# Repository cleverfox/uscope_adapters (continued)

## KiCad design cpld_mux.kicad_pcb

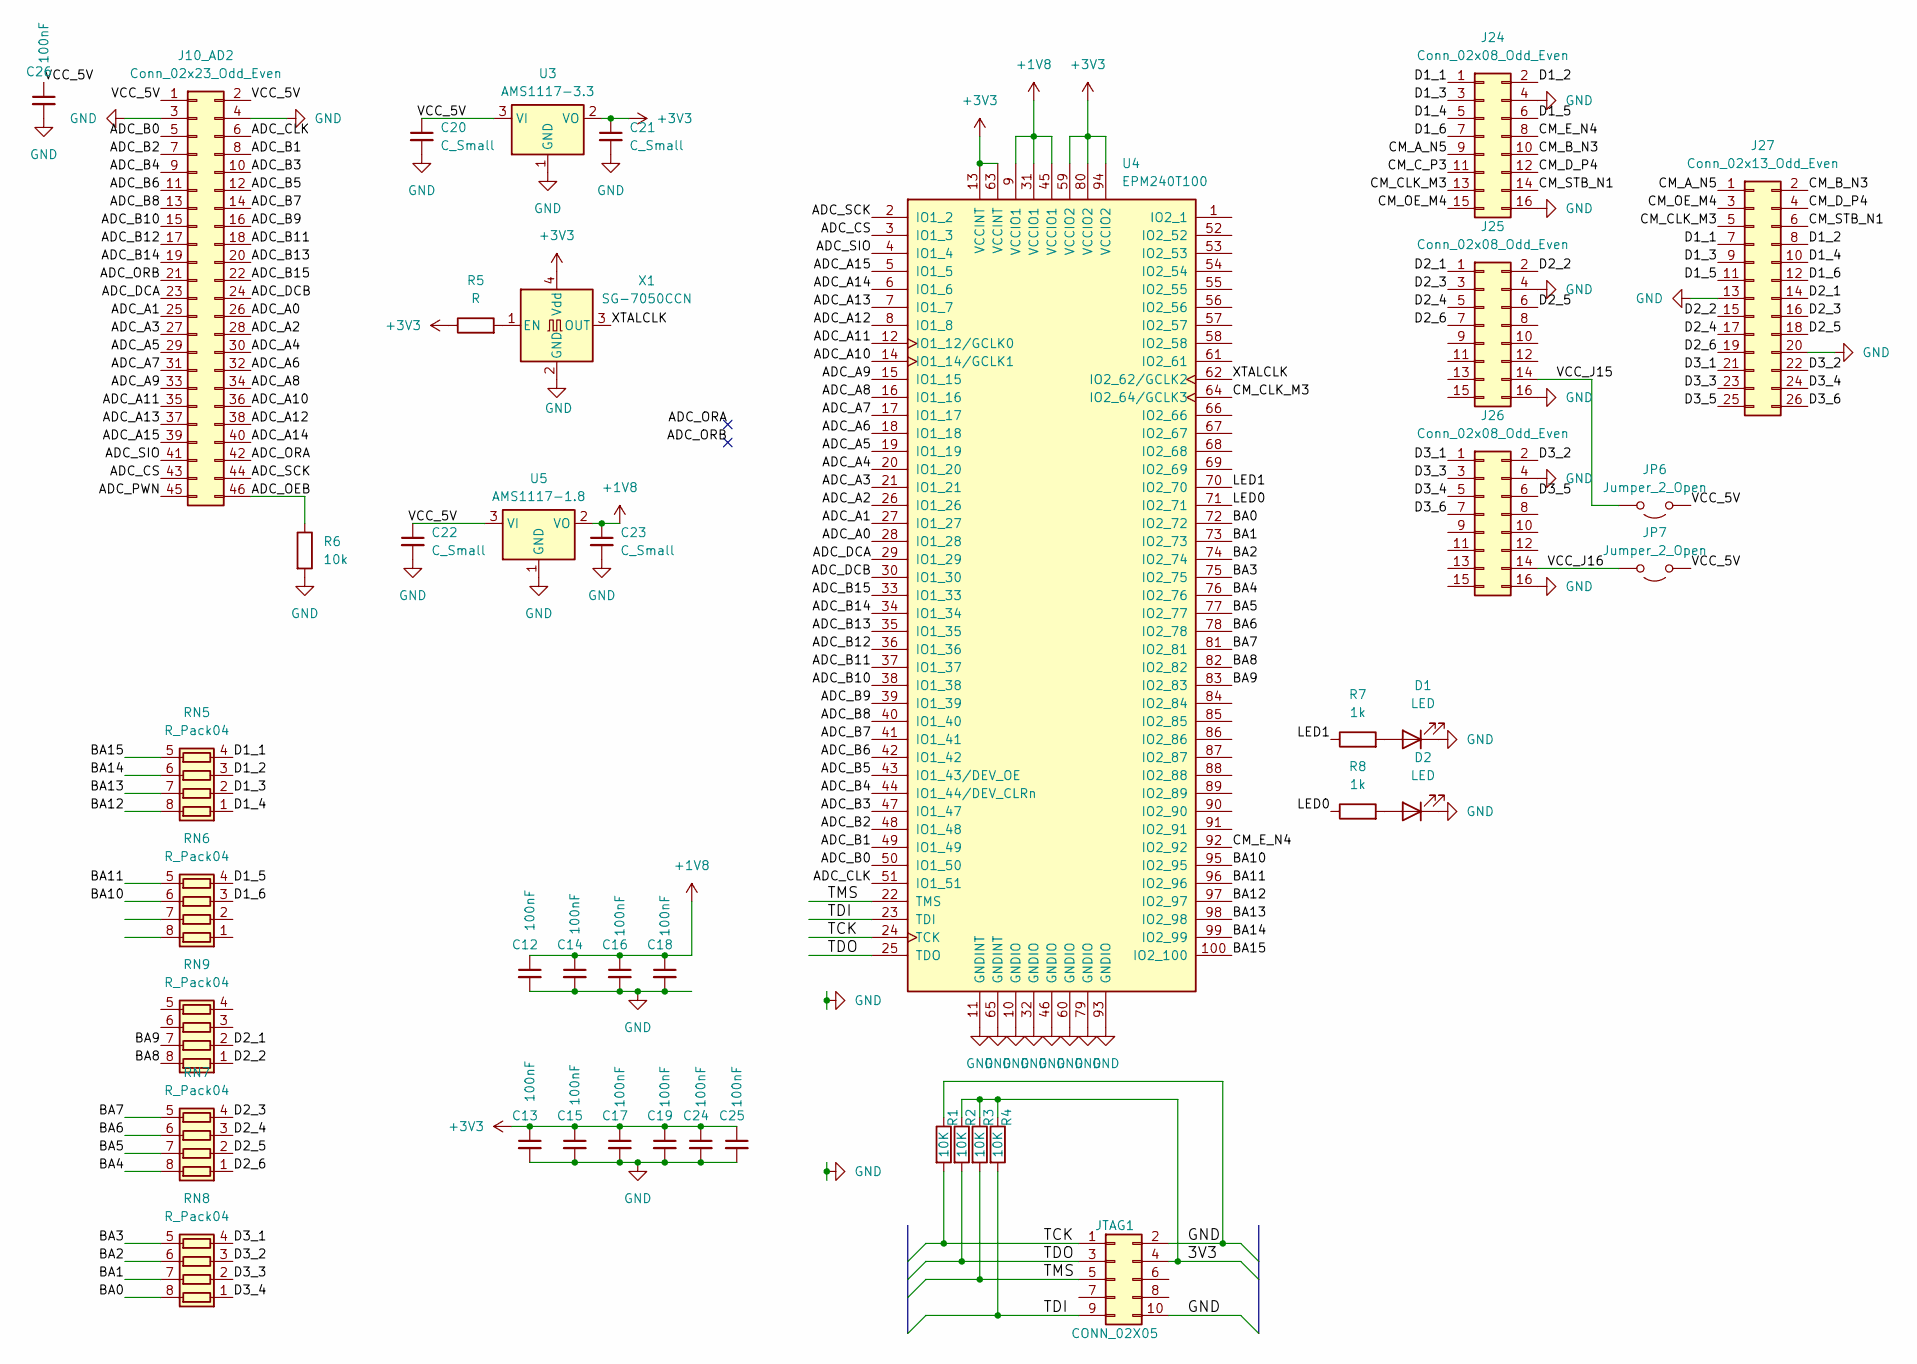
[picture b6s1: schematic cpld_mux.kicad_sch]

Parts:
C12, C13, C14, C15, C16, C17, C18, C19, C24, C25, C26: 100nF; C_0805_2012Metric
C20, C21, C22, C23: C_Small; C_0805_2012Metric
D1, D2: LED; LED_0805_2012Metric
J10_AD2: Conn_02x23_Odd_Even; PinSocket_2x23_P2.54mm_Vertical
J24, J25, J26: Conn_02x08_Odd_Even; PinSocket_2x08_P2.54mm_Vertical
J27: Conn_02x13_Odd_Even; PinHeader_2x13_P2.54mm_Vertical
JP6, JP7: Jumper_2_Open; SolderJumper-3_P1.3mm_Open_Pad1.0x1.5mm
JTAG1: CONN_02X05; PinHeader_2x05_P2.54mm_Vertical
R1, R2, R3, R4: 10K; R_0603_1608Metric_Pad0.98x0.95mm_HandSolder
R5: R; R_0603_1608Metric_Pad0.98x0.95mm_HandSolder
R6: 10k
R7, R8: 1k; R_0805_2012Metric
RN5, RN6, RN7, RN8, RN9: R_Pack04; R_Array_Convex_4x0603
U3: AMS1117-3.3; SOT-223-3_TabPin2
U4: EPM240T100; LQFP-100_14x14mm_P0.5mm
U5: AMS1117-1.8; SOT-223-3_TabPin2
X1: SG-7050CCN; Oscillator_SMD_Abracon_ASV-4Pin_7.0x5.1mm

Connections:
+1V8: C12.1, C14.1, C16.1, C18.1, C23.1, U4.9 (VCCIO1), U4.31 (VCCIO1), U4.45 (VCCIO1), U5.2 (VO)
+3V3: C13.1, C15.1, C17.1, C19.1, C21.1, C24.1, C25.1, R5.1, U3.2 (VO), U4.13 (VCCINT), U4.59 (VCCIO2), U4.63 (VCCINT), U4.80 (VCCIO2), U4.94 (VCCIO2), X1.4 (Vdd)
/cpld_mux/3V3: JTAG1.4, R2.1, R3.1, R4.1
/cpld_mux/ADC_A0: J10_AD2.26, U4.28 (IO1_28)
/cpld_mux/ADC_A1: J10_AD2.25, U4.27 (IO1_27)
/cpld_mux/ADC_A2: J10_AD2.28, U4.26 (IO1_26)
/cpld_mux/ADC_A3: J10_AD2.27, U4.21 (IO1_21)
/cpld_mux/ADC_A4: J10_AD2.30, U4.20 (IO1_20)
/cpld_mux/ADC_A5: J10_AD2.29, U4.19 (IO1_19)
/cpld_mux/ADC_A6: J10_AD2.32, U4.18 (IO1_18)
/cpld_mux/ADC_A7: J10_AD2.31, U4.17 (IO1_17)
/cpld_mux/ADC_A8: J10_AD2.34, U4.16 (IO1_16)
/cpld_mux/ADC_A9: J10_AD2.33, U4.15 (IO1_15)
/cpld_mux/ADC_A10: J10_AD2.36, U4.14 (IO1_14/GCLK1)
/cpld_mux/ADC_A11: J10_AD2.35, U4.12 (IO1_12/GCLK0)
/cpld_mux/ADC_A12: J10_AD2.38, U4.8 (IO1_8)
/cpld_mux/ADC_A13: J10_AD2.37, U4.7 (IO1_7)
/cpld_mux/ADC_A14: J10_AD2.40, U4.6 (IO1_6)
/cpld_mux/ADC_A15: J10_AD2.39, U4.5 (IO1_5)
/cpld_mux/ADC_B0: J10_AD2.5, U4.50 (IO1_50)
/cpld_mux/ADC_B1: J10_AD2.8, U4.49 (IO1_49)
/cpld_mux/ADC_B2: J10_AD2.7, U4.48 (IO1_48)
/cpld_mux/ADC_B3: J10_AD2.10, U4.47 (IO1_47)
/cpld_mux/ADC_B4: J10_AD2.9, U4.44 (IO1_44/DEV_CLRn)
/cpld_mux/ADC_B5: J10_AD2.12, U4.43 (IO1_43/DEV_OE)
/cpld_mux/ADC_B6: J10_AD2.11, U4.42 (IO1_42)
/cpld_mux/ADC_B7: J10_AD2.14, U4.41 (IO1_41)
/cpld_mux/ADC_B8: J10_AD2.13, U4.40 (IO1_40)
/cpld_mux/ADC_B9: J10_AD2.16, U4.39 (IO1_39)
/cpld_mux/ADC_B10: J10_AD2.15, U4.38 (IO1_38)
/cpld_mux/ADC_B11: J10_AD2.18, U4.37 (IO1_37)
/cpld_mux/ADC_B12: J10_AD2.17, U4.36 (IO1_36)
/cpld_mux/ADC_B13: J10_AD2.20, U4.35 (IO1_35)
/cpld_mux/ADC_B14: J10_AD2.19, U4.34 (IO1_34)
/cpld_mux/ADC_B15: J10_AD2.22, U4.33 (IO1_33)
/cpld_mux/ADC_CLK: J10_AD2.6, U4.51 (IO1_51)
/cpld_mux/ADC_CS: J10_AD2.43, U4.3 (IO1_3)
/cpld_mux/ADC_DCA: J10_AD2.23, U4.29 (IO1_29)
/cpld_mux/ADC_DCB: J10_AD2.24, U4.30 (IO1_30)
/cpld_mux/ADC_OEB: J10_AD2.46, R6.1
/cpld_mux/ADC_ORA: J10_AD2.42
/cpld_mux/ADC_ORB: J10_AD2.21
/cpld_mux/ADC_PWN: J10_AD2.45
/cpld_mux/ADC_SCK: J10_AD2.44, U4.2 (IO1_2)
/cpld_mux/ADC_SIO: J10_AD2.41, U4.4 (IO1_4)
/cpld_mux/BA0: RN8.8 (R1.2), U4.72 (IO2_72)
/cpld_mux/BA1: RN8.7 (R2.2), U4.73 (IO2_73)
/cpld_mux/BA2: RN8.6 (R3.2), U4.74 (IO2_74)
/cpld_mux/BA3: RN8.5 (R4.2), U4.75 (IO2_75)
/cpld_mux/BA4: RN7.8 (R1.2), U4.76 (IO2_76)
/cpld_mux/BA5: RN7.7 (R2.2), U4.77 (IO2_77)
/cpld_mux/BA6: RN7.6 (R3.2), U4.78 (IO2_78)
/cpld_mux/BA7: RN7.5 (R4.2), U4.81 (IO2_81)
/cpld_mux/BA8: RN9.8 (R1.2), U4.82 (IO2_82)
/cpld_mux/BA9: RN9.7 (R2.2), U4.83 (IO2_83)
/cpld_mux/BA10: RN6.6 (R3.2), U4.95 (IO2_95)
/cpld_mux/BA11: RN6.5 (R4.2), U4.96 (IO2_96)
/cpld_mux/BA12: RN5.8 (R1.2), U4.97 (IO2_97)
/cpld_mux/BA13: RN5.7 (R2.2), U4.98 (IO2_98)
/cpld_mux/BA14: RN5.6 (R3.2), U4.99 (IO2_99)
/cpld_mux/BA15: RN5.5 (R4.2), U4.100 (IO2_100)
/cpld_mux/CM_A_N5: J24.9, J27.1
/cpld_mux/CM_B_N3: J24.10, J27.2
/cpld_mux/CM_CLK_M3: J24.13, J27.5, U4.64 (IO2_64/GCLK3)
/cpld_mux/CM_C_P3: J24.11
/cpld_mux/CM_D_P4: J24.12, J27.4
/cpld_mux/CM_E_N4: J24.8, U4.92 (IO2_92)
/cpld_mux/CM_OE_M4: J24.15, J27.3
/cpld_mux/CM_STB_N1: J24.14, J27.6
/cpld_mux/D1_1: J24.1, J27.7, RN5.4 (R4.1)
/cpld_mux/D1_2: J24.2, J27.8, RN5.3 (R3.1)
/cpld_mux/D1_3: J24.3, J27.9, RN5.2 (R2.1)
/cpld_mux/D1_4: J24.5, J27.10, RN5.1 (R1.1)
/cpld_mux/D1_5: J24.6, J27.11, RN6.4 (R4.1)
/cpld_mux/D1_6: J24.7, J27.12, RN6.3 (R3.1)
/cpld_mux/D2_1: J25.1, J27.14, RN9.2 (R2.1)
/cpld_mux/D2_2: J25.2, J27.15, RN9.1 (R1.1)
/cpld_mux/D2_3: J25.3, J27.16, RN7.4 (R4.1)
/cpld_mux/D2_4: J25.5, J27.17, RN7.3 (R3.1)
/cpld_mux/D2_5: J25.6, J27.18, RN7.2 (R2.1)
/cpld_mux/D2_6: J25.7, J27.19, RN7.1 (R1.1)
/cpld_mux/D3_1: J26.1, J27.21, RN8.4 (R4.1)
/cpld_mux/D3_2: J26.2, J27.22, RN8.3 (R3.1)
/cpld_mux/D3_3: J26.3, J27.23, RN8.2 (R2.1)
/cpld_mux/D3_4: J26.5, J27.24, RN8.1 (R1.1)
/cpld_mux/D3_5: J26.6, J27.25
/cpld_mux/D3_6: J26.7, J27.26
/cpld_mux/LED0: R8.1, U4.71 (IO2_71)
/cpld_mux/LED1: R7.1, U4.70 (IO2_70)
/cpld_mux/TCK: JTAG1.1, R1.2, U4.24 (TCK)
/cpld_mux/TDI: JTAG1.9, R4.2, U4.23 (TDI)
/cpld_mux/TDO: JTAG1.3, R2.2, U4.25 (TDO)
/cpld_mux/TMS: JTAG1.5, R3.2, U4.22 (TMS)
/cpld_mux/VCC_5V: C20.1, C22.1, C26.1, J10_AD2.1, J10_AD2.2, JP6.1 (A), JP7.1 (A), U3.3 (VI), U5.3 (VI)
/cpld_mux/VCC_J15: J25.14, JP6.2 (B)
/cpld_mux/VCC_J16: J26.14, JP7.2 (B)
/cpld_mux/XTALCLK: U4.62 (IO2_62/GCLK2), X1.3 (OUT)
GND: C12.2, C13.2, C14.2, C15.2, C16.2, C17.2, C18.2, C19.2, C20.2, C21.2, C22.2, C23.2, C24.2, C25.2, C26.2, D1.1 (K), D2.1 (K), J10_AD2.3, J10_AD2.4, J24.4, J24.16, J25.4, J25.16, J26.4, J26.16, J27.13, J27.20, JTAG1.2, JTAG1.10, R1.1, R6.2, U3.1 (GND), U4.10 (GNDIO), U4.11 (GNDINT), U4.32 (GNDIO), U4.46 (GNDIO), U4.60 (GNDIO), U4.65 (GNDINT), U4.79 (GNDIO), U4.93 (GNDIO), U5.1 (GND), X1.2 (GND)
unnamed: D1.2 (A), R7.2
unnamed: D2.2 (A), R8.2
unnamed: R5.2, X1.1 (EN)

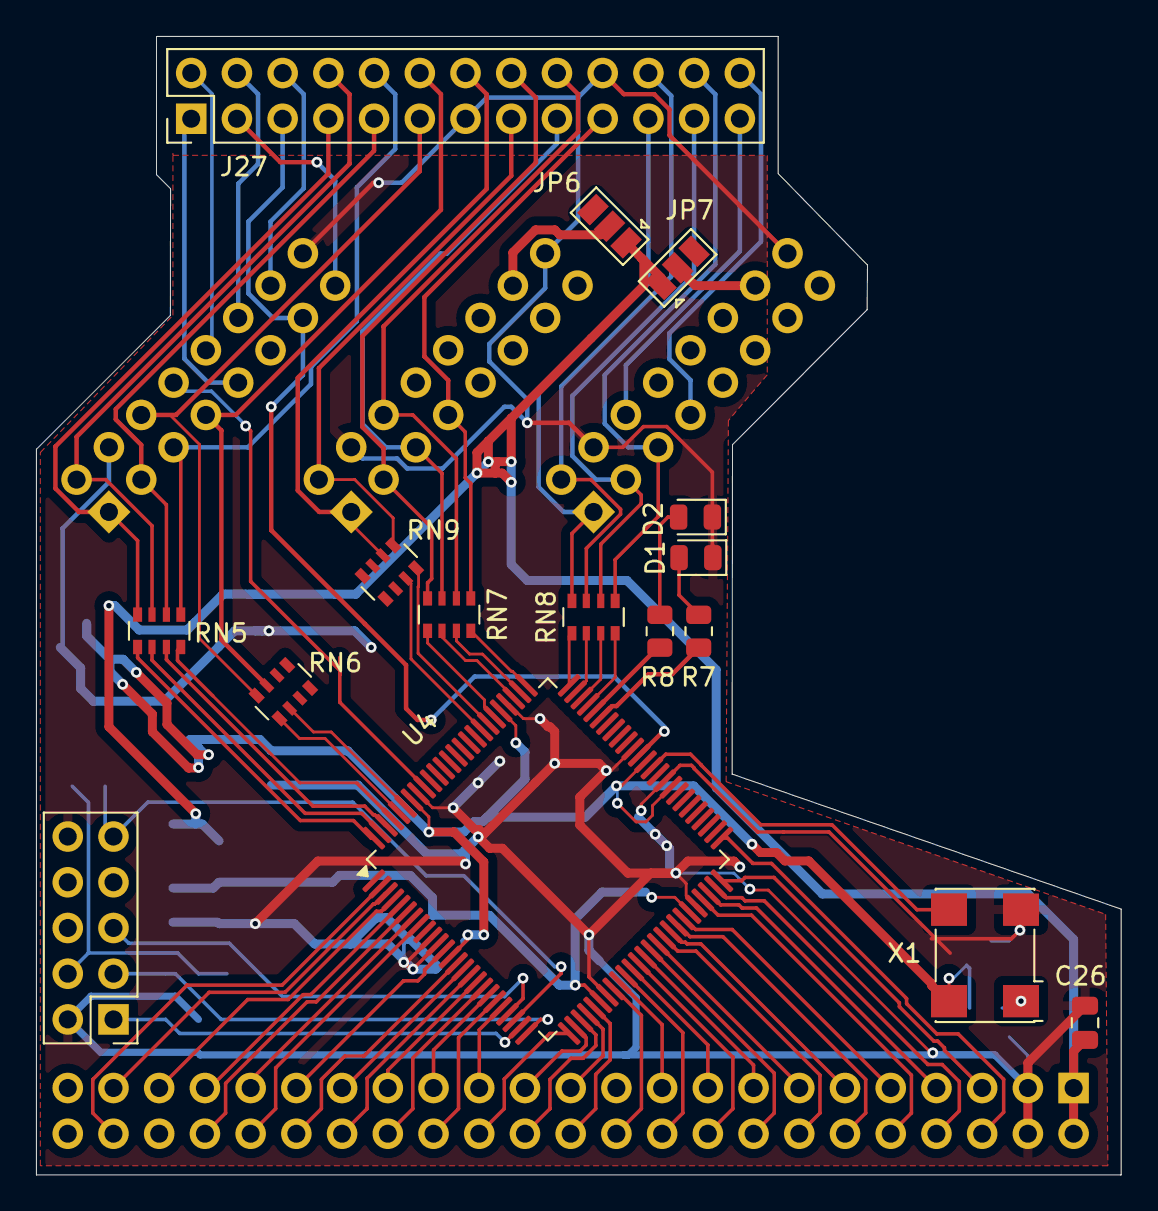
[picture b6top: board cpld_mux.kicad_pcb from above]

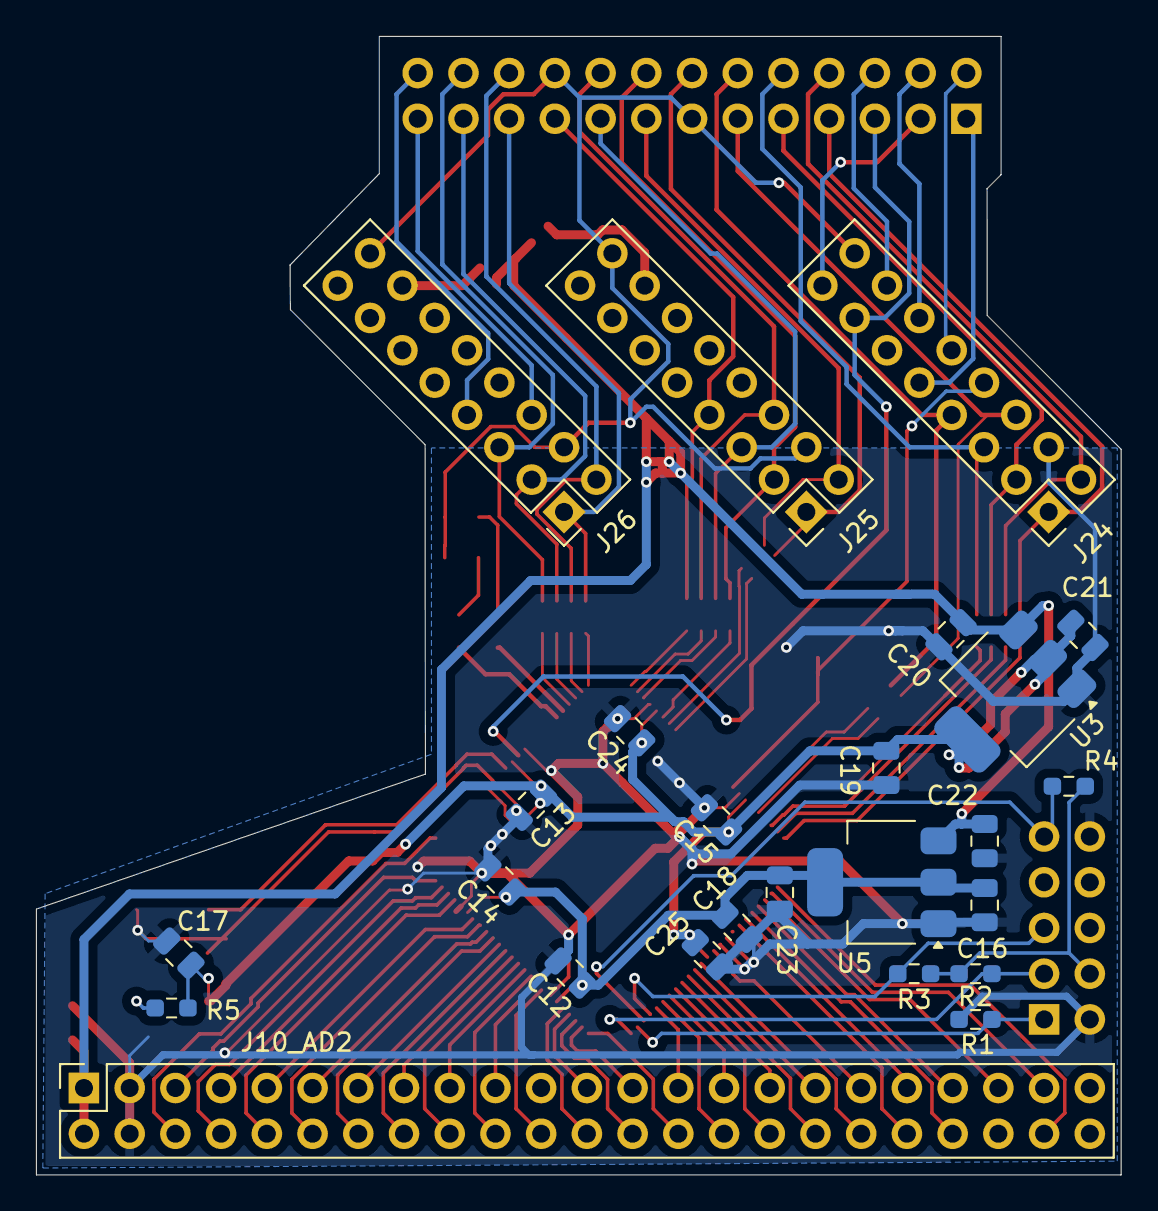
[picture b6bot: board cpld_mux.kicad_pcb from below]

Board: 2 copper layers, 60.3 x 63.3 mm, 41 parts (25 on the bottom side), 96 nets.

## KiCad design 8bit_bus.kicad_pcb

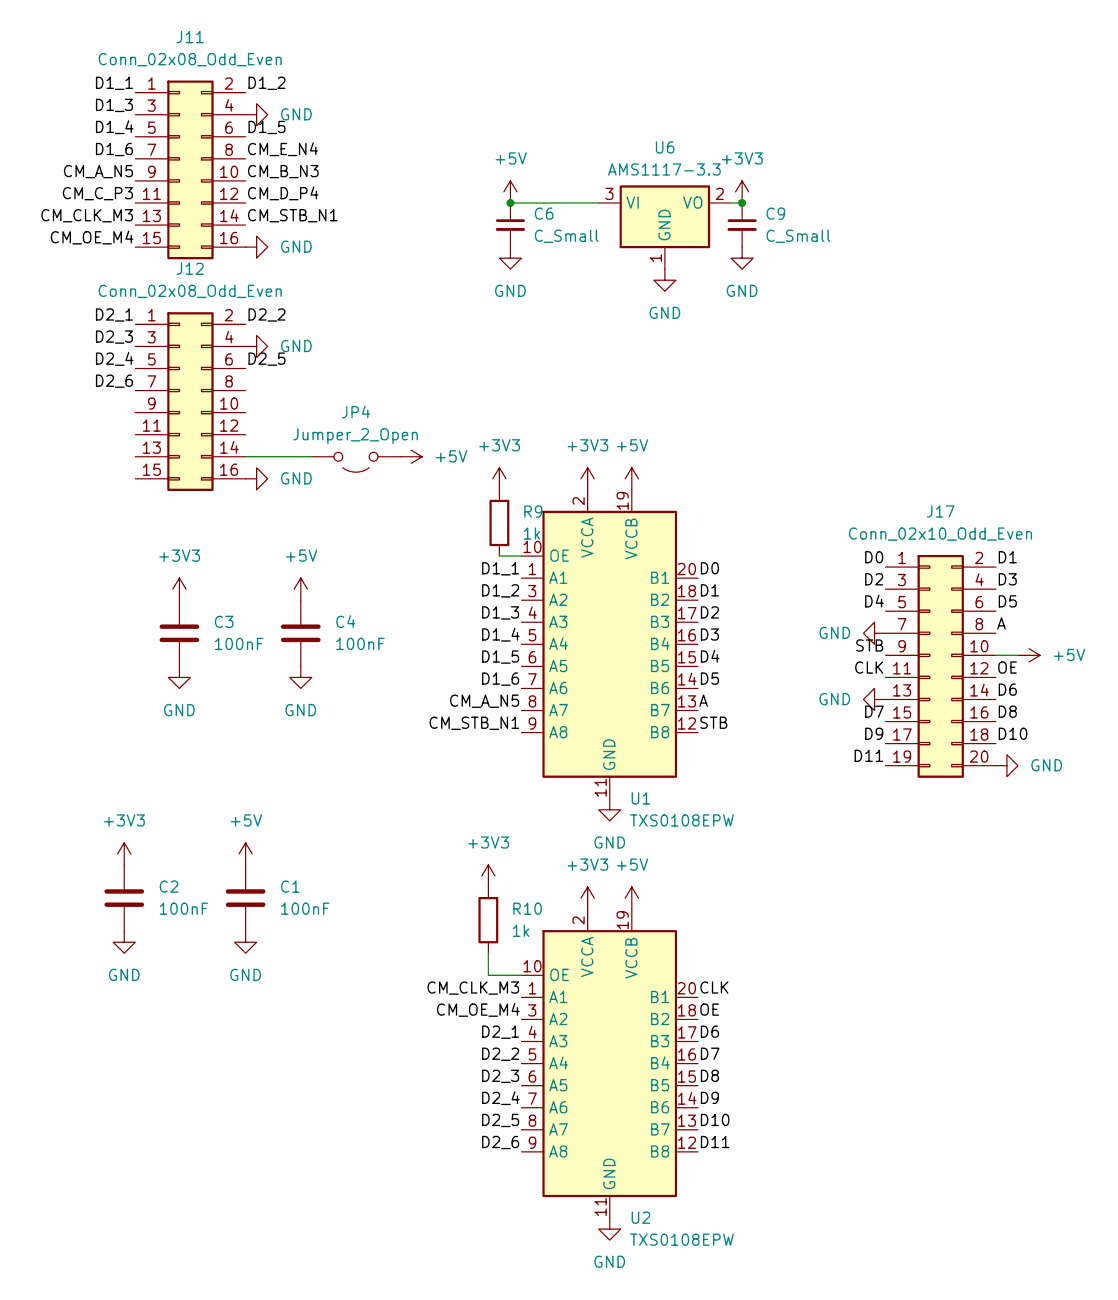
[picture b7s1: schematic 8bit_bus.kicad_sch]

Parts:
C1, C2, C3, C4: 100nF; C_0805_2012Metric
C6, C9: C_Small; C_0805_2012Metric
J11, J12: Conn_02x08_Odd_Even; PinSocket_2x08_P2.54mm_Vertical
J17: Conn_02x10_Odd_Even; PinHeader_2x10_P2.54mm_Vertical
JP4: Jumper_2_Open; SolderJumper-3_P1.3mm_Open_Pad1.0x1.5mm
R9, R10: 1k; R_0805_2012Metric
U1, U2: TXS0108EPW; TSSOP-20_4.4x6.5mm_P0.65mm
U6: AMS1117-3.3; SOT-223-3_TabPin2

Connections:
+3V3: C2.1, C3.1, C9.1, R9.2, R10.2, U1.2 (VCCA), U2.2 (VCCA), U6.2 (VO)
+5V: C1.1, C4.1, C6.1, J17.10, JP4.1 (A), U1.19 (VCCB), U2.19 (VCCB), U6.3 (VI)
/8bit_bus/A: J17.8, U1.13 (B7)
/8bit_bus/CLK: J17.11, U2.20 (B1)
/8bit_bus/CM_A_N5: J11.9, U1.8 (A7)
/8bit_bus/CM_B_N3: J11.10
/8bit_bus/CM_CLK_M3: J11.13, U2.1 (A1)
/8bit_bus/CM_C_P3: J11.11
/8bit_bus/CM_D_P4: J11.12
/8bit_bus/CM_E_N4: J11.8
/8bit_bus/CM_OE_M4: J11.15, U2.3 (A2)
/8bit_bus/CM_STB_N1: J11.14, U1.9 (A8)
/8bit_bus/D0: J17.1, U1.20 (B1)
/8bit_bus/D1: J17.2, U1.18 (B2)
/8bit_bus/D1_1: J11.1, U1.1 (A1)
/8bit_bus/D1_2: J11.2, U1.3 (A2)
/8bit_bus/D1_3: J11.3, U1.4 (A3)
/8bit_bus/D1_4: J11.5, U1.5 (A4)
/8bit_bus/D1_5: J11.6, U1.6 (A5)
/8bit_bus/D1_6: J11.7, U1.7 (A6)
/8bit_bus/D2: J17.3, U1.17 (B3)
/8bit_bus/D2_1: J12.1, U2.4 (A3)
/8bit_bus/D2_2: J12.2, U2.5 (A4)
/8bit_bus/D2_3: J12.3, U2.6 (A5)
/8bit_bus/D2_4: J12.5, U2.7 (A6)
/8bit_bus/D2_5: J12.6, U2.8 (A7)
/8bit_bus/D2_6: J12.7, U2.9 (A8)
/8bit_bus/D3: J17.4, U1.16 (B4)
/8bit_bus/D4: J17.5, U1.15 (B5)
/8bit_bus/D5: J17.6, U1.14 (B6)
/8bit_bus/D6: J17.14, U2.17 (B3)
/8bit_bus/D7: J17.15, U2.16 (B4)
/8bit_bus/D8: J17.16, U2.15 (B5)
/8bit_bus/D9: J17.17, U2.14 (B6)
/8bit_bus/D10: J17.18, U2.13 (B7)
/8bit_bus/D11: J17.19, U2.12 (B8)
/8bit_bus/OE: J17.12, U2.18 (B2)
/8bit_bus/STB: J17.9, U1.12 (B8)
GND: C1.2, C2.2, C3.2, C4.2, C6.2, C9.2, J11.4, J11.16, J12.4, J12.16, J17.7, J17.13, J17.20, U1.11 (GND), U2.11 (GND), U6.1 (GND)
unnamed: J12.14, JP4.2 (B)
unnamed: R9.1, U1.10 (OE)
unnamed: R10.1, U2.10 (OE)

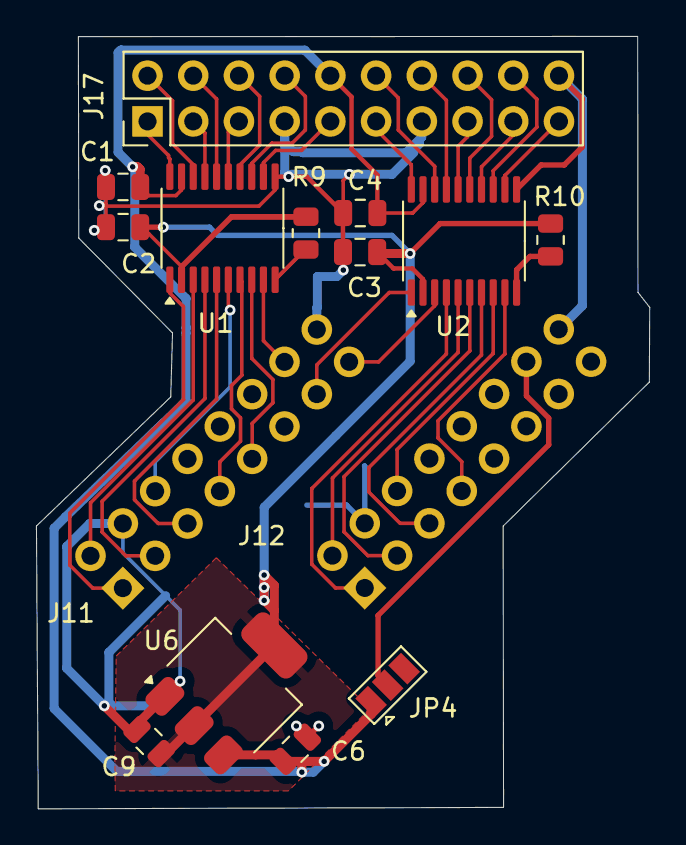
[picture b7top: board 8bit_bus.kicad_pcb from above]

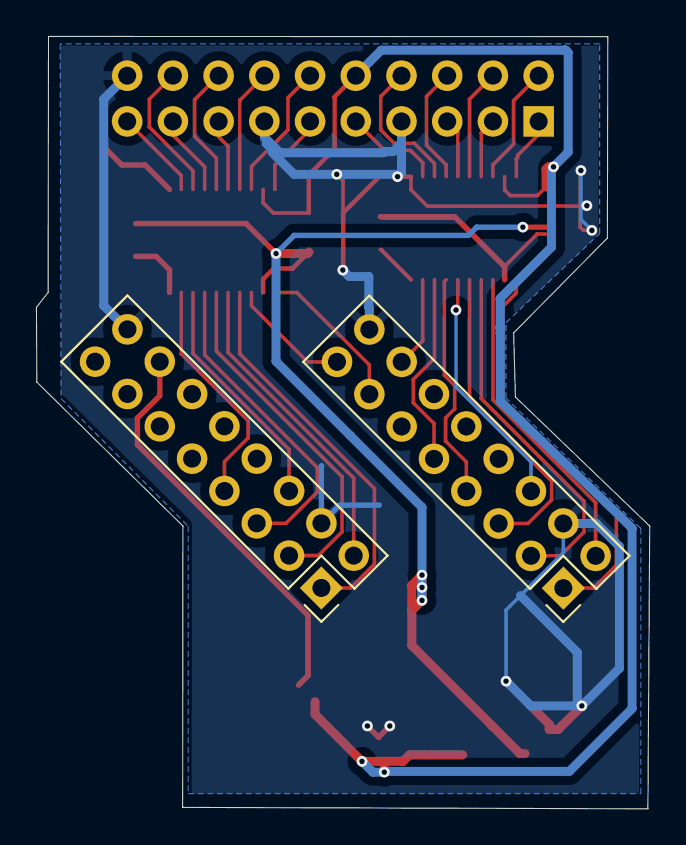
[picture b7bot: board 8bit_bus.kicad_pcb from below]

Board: 2 copper layers, 34.1 x 42.9 mm, 15 parts (2 on the bottom side), 38 nets.

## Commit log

2024-12-17 first ordered gerbers
